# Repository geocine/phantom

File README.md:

# Phantom

An ortholinear WASD optimized gaming keypad

<div align="center">
  
</div>
</br/>

If you are looking for version 1 please check the [v1 tag](https://github.com/geocine/Geopad/tree/v1)

## Design Files
Design files are all on the cloud
- [PCB (EasyEDA)](https://easyeda.com/geocipher/phantom)
- [Case (Onshape)](https://cad.onshape.com/documents/dbda5693b40a7bc2ccdd639a/w/846729df4491243848816a00/e/3b0d7331e1da385ccecf5c3d)
- [Keyboard Layout Editor](http://www.keyboard-layout-editor.com/#/gists/be78f234d304392bfcd8f41bcfa9a9c5)

## Usage

This keyboard supports *via* , just compile the *via* keymap through `qmk`. Or, flash the built `geopad_phantom_via.hex`.

```
make geocine/phantom:via
```
To flash the firmware, you can either use the QMK Toolbox GUI or through this command
```
qmk flash -kb geocine/phantom -km via
```
Once via is running you can import the keymap `firmware/keymaps/via/phantom.json`

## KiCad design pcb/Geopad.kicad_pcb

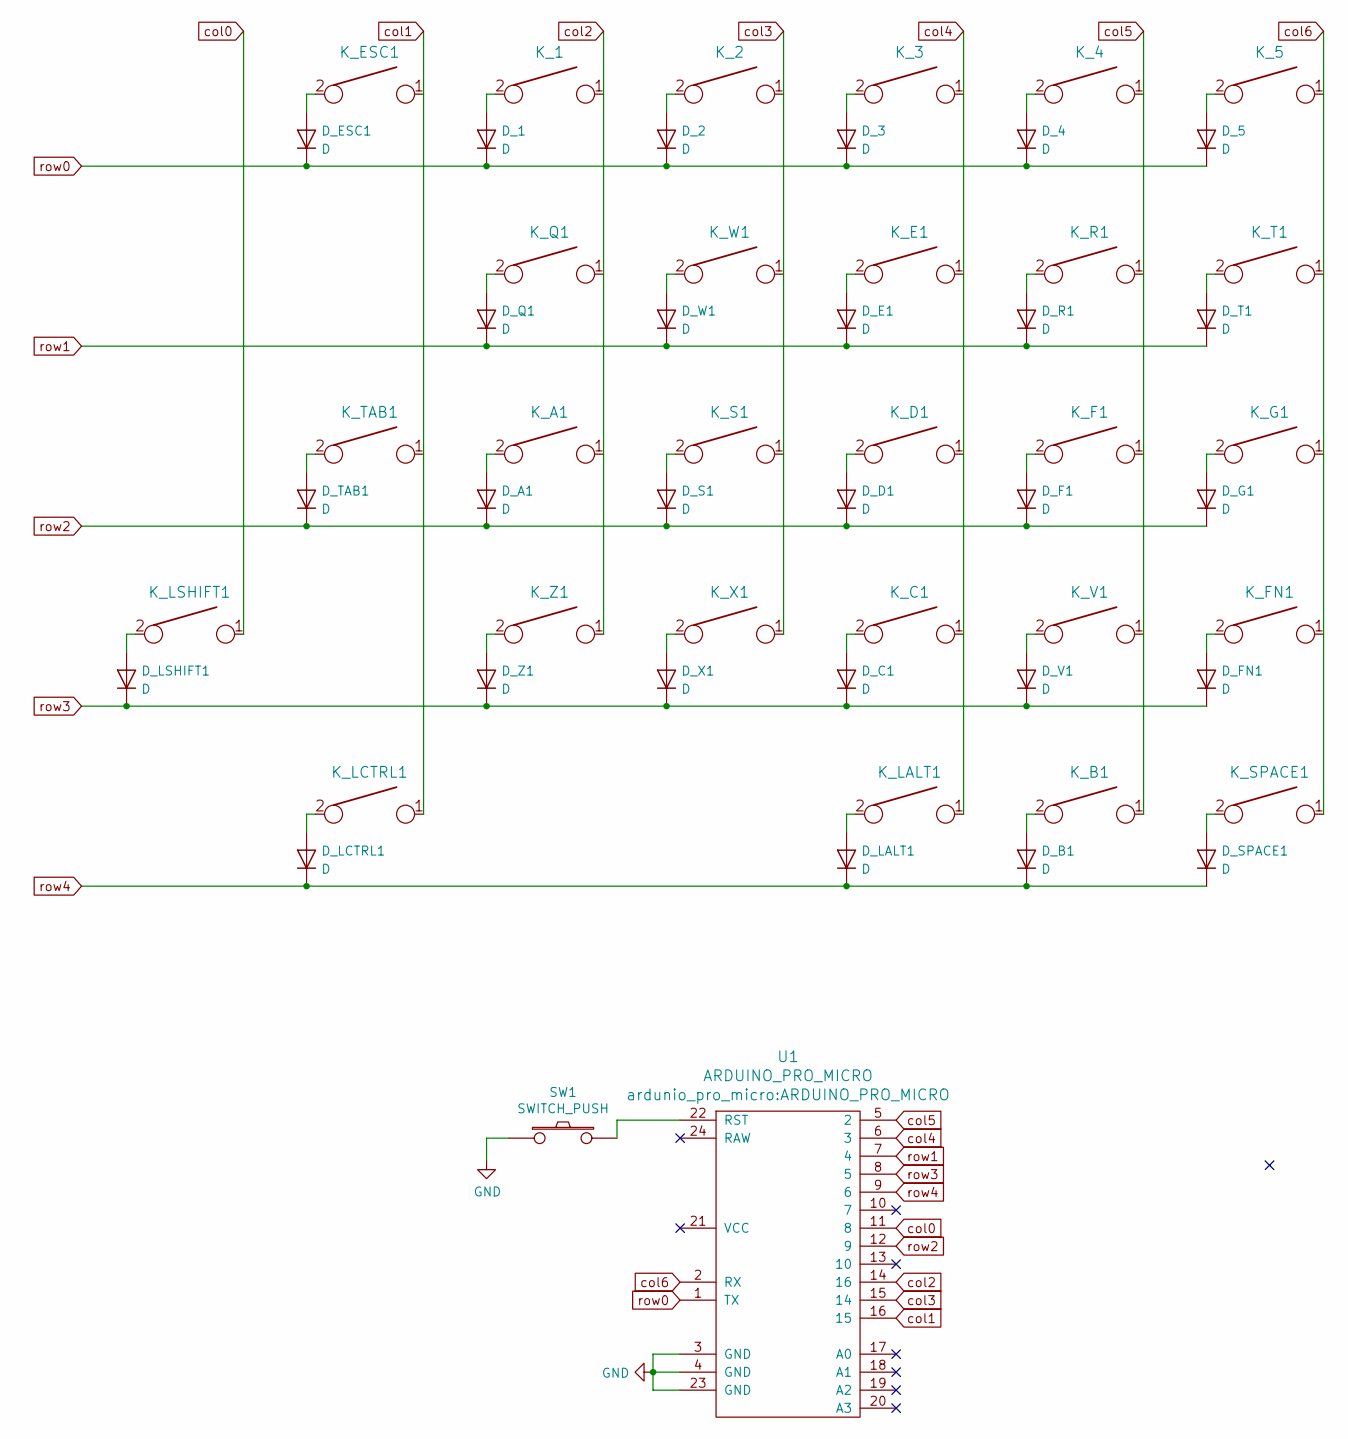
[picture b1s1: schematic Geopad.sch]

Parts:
D_1, D_2, D_3, D_4, D_5: D; D_SOD123_axial
D_A1: D; D_SOD123_axial
D_B1: D; D_SOD123_axial
D_C1: D; D_SOD123_axial
D_D1: D; D_SOD123_axial
D_E1: D; D_SOD123_axial
D_ESC1: D; D_SOD123_axial
D_F1: D; D_SOD123_axial
D_FN1: D; D_SOD123_axial
D_G1: D; D_SOD123_axial
D_LALT1: D; D_SOD123_axial
D_LCTRL1: D; D_SOD123_axial
D_LSHIFT1: D; D_SOD123_axial
D_Q1: D; D_SOD123_axial
D_R1: D; D_SOD123_axial
D_S1: D; D_SOD123_axial
D_SPACE1: D; D_SOD123_axial
D_T1: D; D_SOD123_axial
D_TAB1: D; D_SOD123_axial
D_V1: D; D_SOD123_axial
D_W1: D; D_SOD123_axial
D_X1: D; D_SOD123_axial
D_Z1: D; D_SOD123_axial
K_1, K_2, K_3, K_4, K_5: KEYSW; MX-1U-NoLED
K_A1: KEYSW; MX-1U-NoLED
K_B1: KEYSW; MX-1U-NoLED
K_C1: KEYSW; MX-1U-NoLED
K_D1: KEYSW; MX-1U-NoLED
K_E1: KEYSW; MX-1U-NoLED
K_ESC1: KEYSW; MX-1U-NoLED
K_F1: KEYSW; MX-1U-NoLED
K_FN1: KEYSW; MX-1U-NoLED
K_G1: KEYSW; MX-1U-NoLED
K_LALT1: KEYSW; MX-1U-NoLED
K_LCTRL1: KEYSW; MX-1U-NoLED
K_LSHIFT1: KEYSW; MX-1U-NoLED
K_Q1: KEYSW; MX-1U-NoLED
K_R1: KEYSW; MX-1U-NoLED
K_S1: KEYSW; MX-1U-NoLED
K_SPACE1: KEYSW; MX-1U-NoLED
K_T1: KEYSW; MX-1U-NoLED
K_TAB1: KEYSW; MX-1U-NoLED
K_V1: KEYSW; MX-1U-NoLED
K_W1: KEYSW; MX-1U-NoLED
K_X1: KEYSW; MX-1U-NoLED
K_Z1: KEYSW; MX-1U-NoLED
SW1: SWITCH_PUSH; SW_SPST_TL3342
U1: ARDUINO_PRO_MICRO

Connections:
GND: SW1.1, U1.3 (GND), U1.4 (GND), U1.23 (GND)
unnamed: D_1.2 (A), K_1.2
unnamed: D_2.2 (A), K_2.2
unnamed: D_3.2 (A), K_3.2
unnamed: D_4.2 (A), K_4.2
unnamed: D_5.2 (A), K_5.2
unnamed: D_A1.2 (A), K_A1.2
unnamed: D_B1.2 (A), K_B1.2
unnamed: D_C1.2 (A), K_C1.2
unnamed: D_D1.2 (A), K_D1.2
unnamed: D_E1.2 (A), K_E1.2
unnamed: D_ESC1.2 (A), K_ESC1.2
unnamed: D_F1.2 (A), K_F1.2
unnamed: D_FN1.2 (A), K_FN1.2
unnamed: D_G1.2 (A), K_G1.2
unnamed: D_LALT1.2 (A), K_LALT1.2
unnamed: D_LCTRL1.2 (A), K_LCTRL1.2
unnamed: D_LSHIFT1.2 (A), K_LSHIFT1.2
unnamed: D_Q1.2 (A), K_Q1.2
unnamed: D_R1.2 (A), K_R1.2
unnamed: D_S1.2 (A), K_S1.2
unnamed: D_SPACE1.2 (A), K_SPACE1.2
unnamed: D_T1.2 (A), K_T1.2
unnamed: D_TAB1.2 (A), K_TAB1.2
unnamed: D_V1.2 (A), K_V1.2
unnamed: D_W1.2 (A), K_W1.2
unnamed: D_X1.2 (A), K_X1.2
unnamed: D_Z1.2 (A), K_Z1.2
unnamed: SW1.2, U1.22 (RST)
col0: K_LSHIFT1.1, U1.11 (8)
col1: K_ESC1.1, K_LCTRL1.1, K_TAB1.1, U1.16 (15)
col2: K_1.1, K_A1.1, K_Q1.1, K_Z1.1, U1.14 (16)
col3: K_2.1, K_S1.1, K_W1.1, K_X1.1, U1.15 (14)
col4: K_3.1, K_C1.1, K_D1.1, K_E1.1, K_LALT1.1, U1.6 (3)
col5: K_4.1, K_B1.1, K_F1.1, K_R1.1, K_V1.1, U1.5 (2)
col6: K_5.1, K_FN1.1, K_G1.1, K_SPACE1.1, K_T1.1, U1.2 (RX)
row0: D_1.1 (K), D_2.1 (K), D_3.1 (K), D_4.1 (K), D_5.1 (K), D_ESC1.1 (K), U1.1 (TX)
row1: D_E1.1 (K), D_Q1.1 (K), D_R1.1 (K), D_T1.1 (K), D_W1.1 (K), U1.7 (4)
row2: D_A1.1 (K), D_D1.1 (K), D_F1.1 (K), D_G1.1 (K), D_S1.1 (K), D_TAB1.1 (K), U1.12 (9)
row3: D_C1.1 (K), D_FN1.1 (K), D_LSHIFT1.1 (K), D_V1.1 (K), D_X1.1 (K), D_Z1.1 (K), U1.8 (5)
row4: D_B1.1 (K), D_LALT1.1 (K), D_LCTRL1.1 (K), D_SPACE1.1 (K), U1.9 (6)

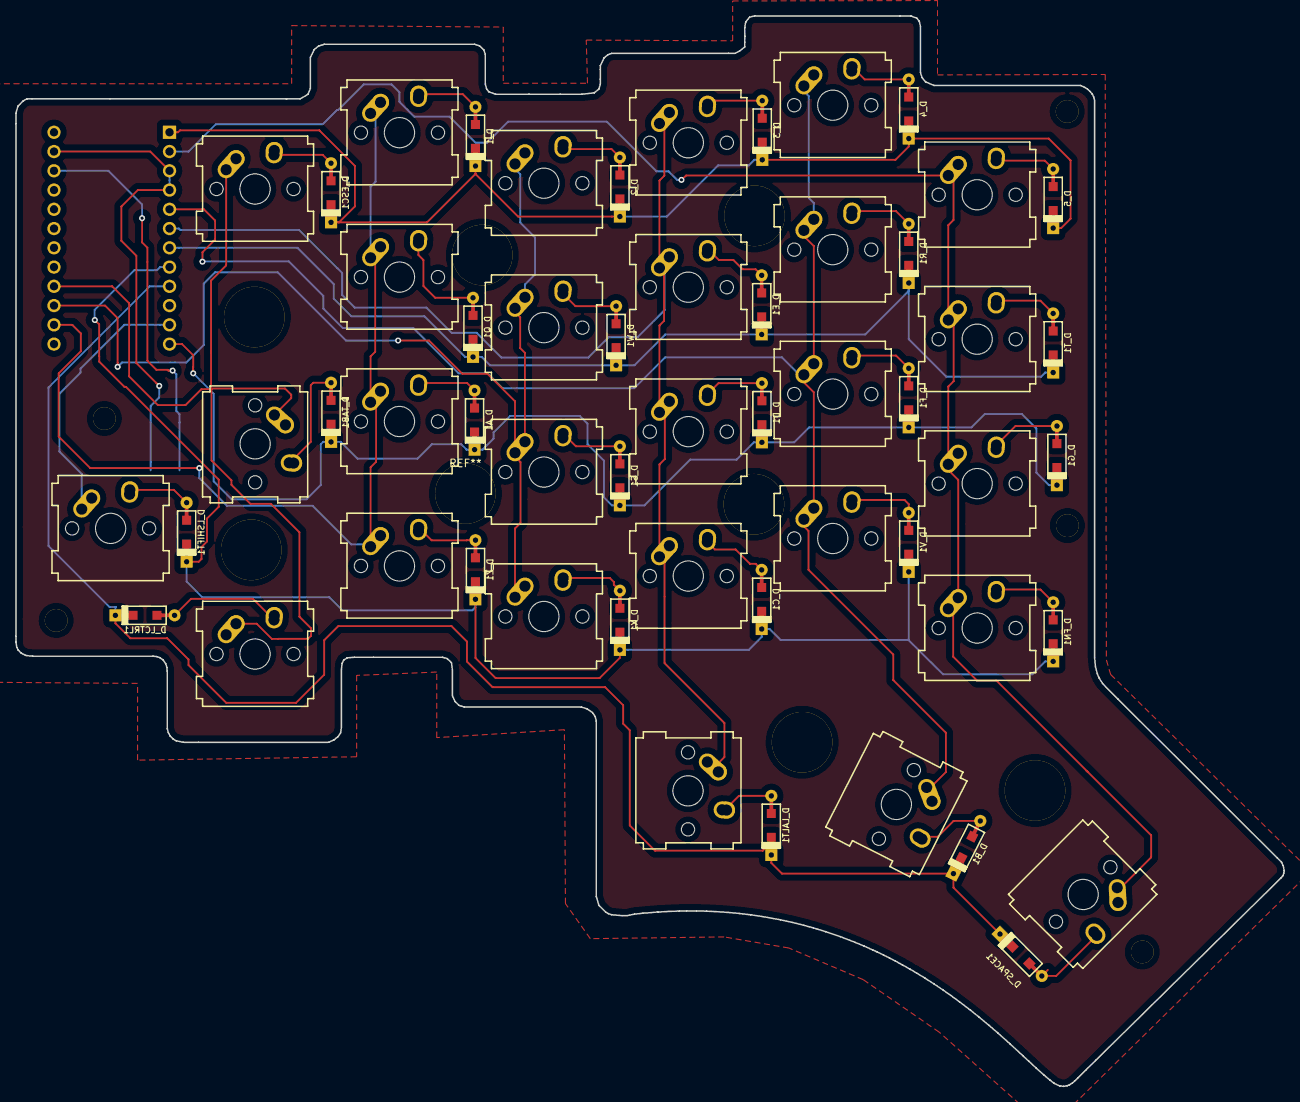
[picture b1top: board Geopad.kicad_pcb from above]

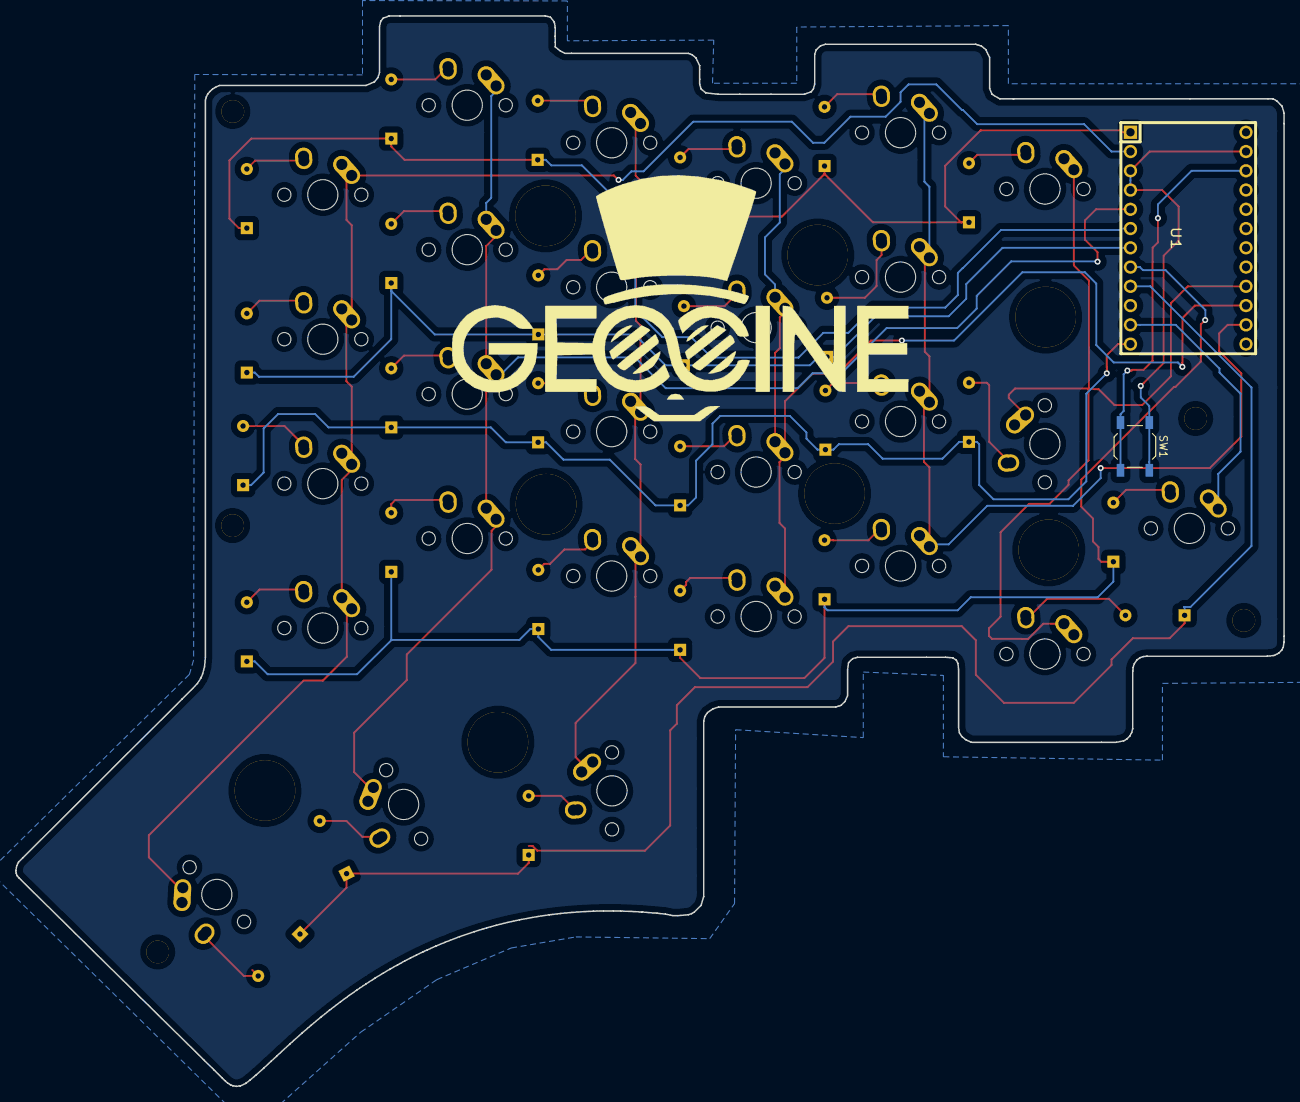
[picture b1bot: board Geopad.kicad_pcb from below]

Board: 2 copper layers, 167.3 x 141.2 mm, 56 parts (2 on the bottom side), 41 nets.

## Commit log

2020-08-31 chore(init): initial commit
2020-10-30 update README and link new PCB
2020-10-30 Update README and link new case
2020-10-30 Update firmware binary and via defintion
2020-10-30 update firmware to use new matrix
2020-12-10 change bootloader to atmel-dfu
